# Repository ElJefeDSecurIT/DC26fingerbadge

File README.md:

# DC26fingerbadge
DEFCON26 Middle Finger Badge

This repository will eventually hold details for the defcon26 2018 middle finger shitty add-on badge, made with a trinket and 3 neopixels, and eagle CAD. Additionally, this repository will eventually be filled out all the details/instructions for making and printing your own badge.

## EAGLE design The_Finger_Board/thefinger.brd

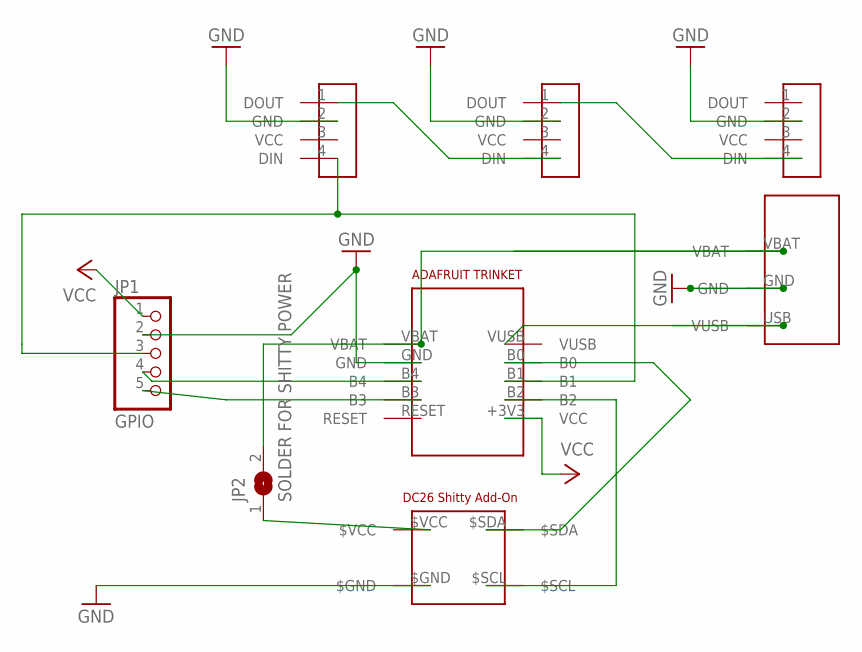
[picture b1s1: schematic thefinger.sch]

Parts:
JP1: GPIO; 1X05
JP2: SOLDER FOR SHITTY POWER; SJW
U$1, U$2, U$4: NEOPIXEL5MMRGB
U$3: SHITTYADDON
U$5: ADAFRUIT_TRINKET_3V; ADAFRUIT_TRINKET_3V_MICROUSB
U$6: LIPOPACK

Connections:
$VCC: JP2.1, U$3.$VCC
GND: JP1.2, U$1.2 (GND), U$2.2 (GND), U$3.$GND, U$4.2 (GND), U$5.GND, U$6.GND
unnamed: U$3.$SDA, U$5.B0
unnamed: JP1.5, U$5.B3
unnamed: JP1.3, U$1.4 (DIN), U$5.B1
unnamed: U$1.1 (DOUT), U$2.4 (DIN)
unnamed: U$2.1 (DOUT), U$4.4 (DIN)
unnamed: U$3.$SCL, U$5.B2
S$1: JP1.4, U$5.B4
VBAT: JP2.2, U$5.VBAT, U$6.VBAT
VCC: JP1.1, U$1.3 (VCC), U$2.3 (VCC), U$4.3 (VCC), U$5.+3V3 (VCC)
VUSB: U$5.VUSB, U$6.USB (VUSB)

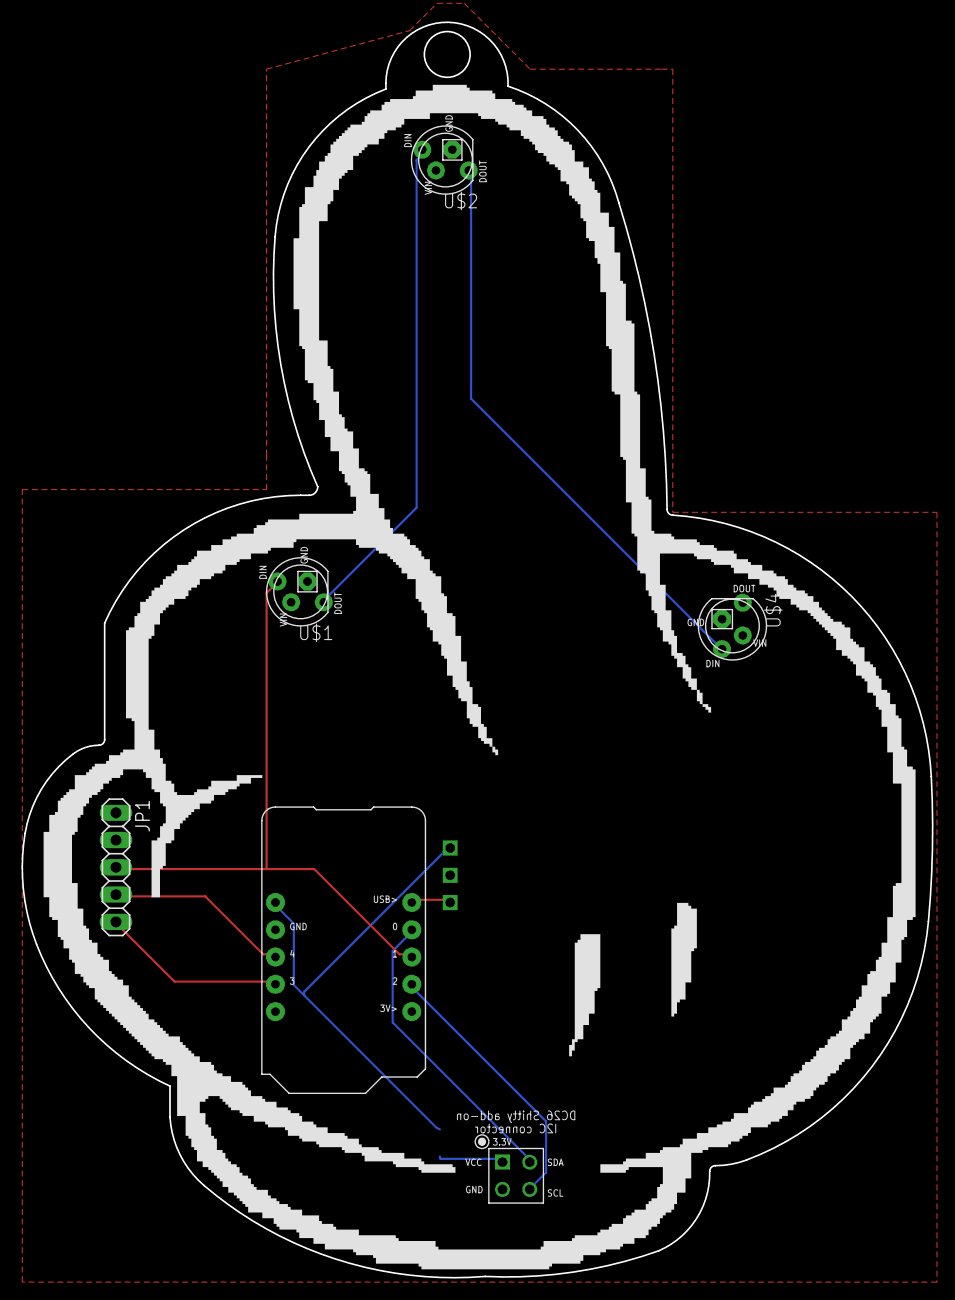
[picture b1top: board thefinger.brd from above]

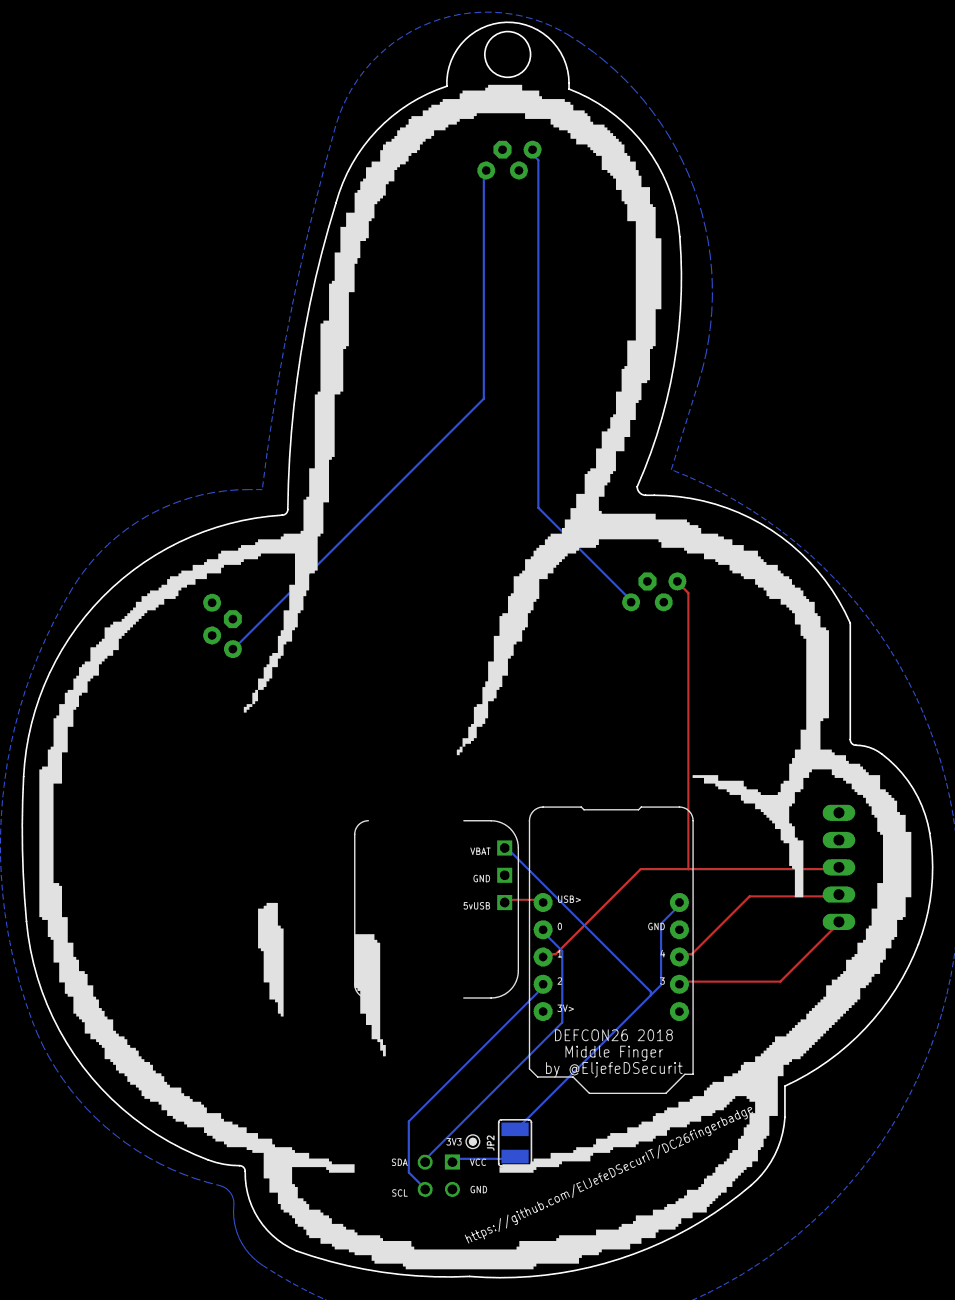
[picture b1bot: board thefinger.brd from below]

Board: 2 copper layers, 84.8 x 116.9 mm, 8 parts (2 on the bottom side), 12 nets.

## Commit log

2018-07-13 Grammar-fixes
2018-07-31 Upload of the badge schematic and brd file.
2018-08-06 circuitpython code for badges.
